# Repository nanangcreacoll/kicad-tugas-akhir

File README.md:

# Desain Skematik dan PCB IoT Liquid Dispensing Kapsul Radiofarmaka I-131

**Skematik**

**PCB**

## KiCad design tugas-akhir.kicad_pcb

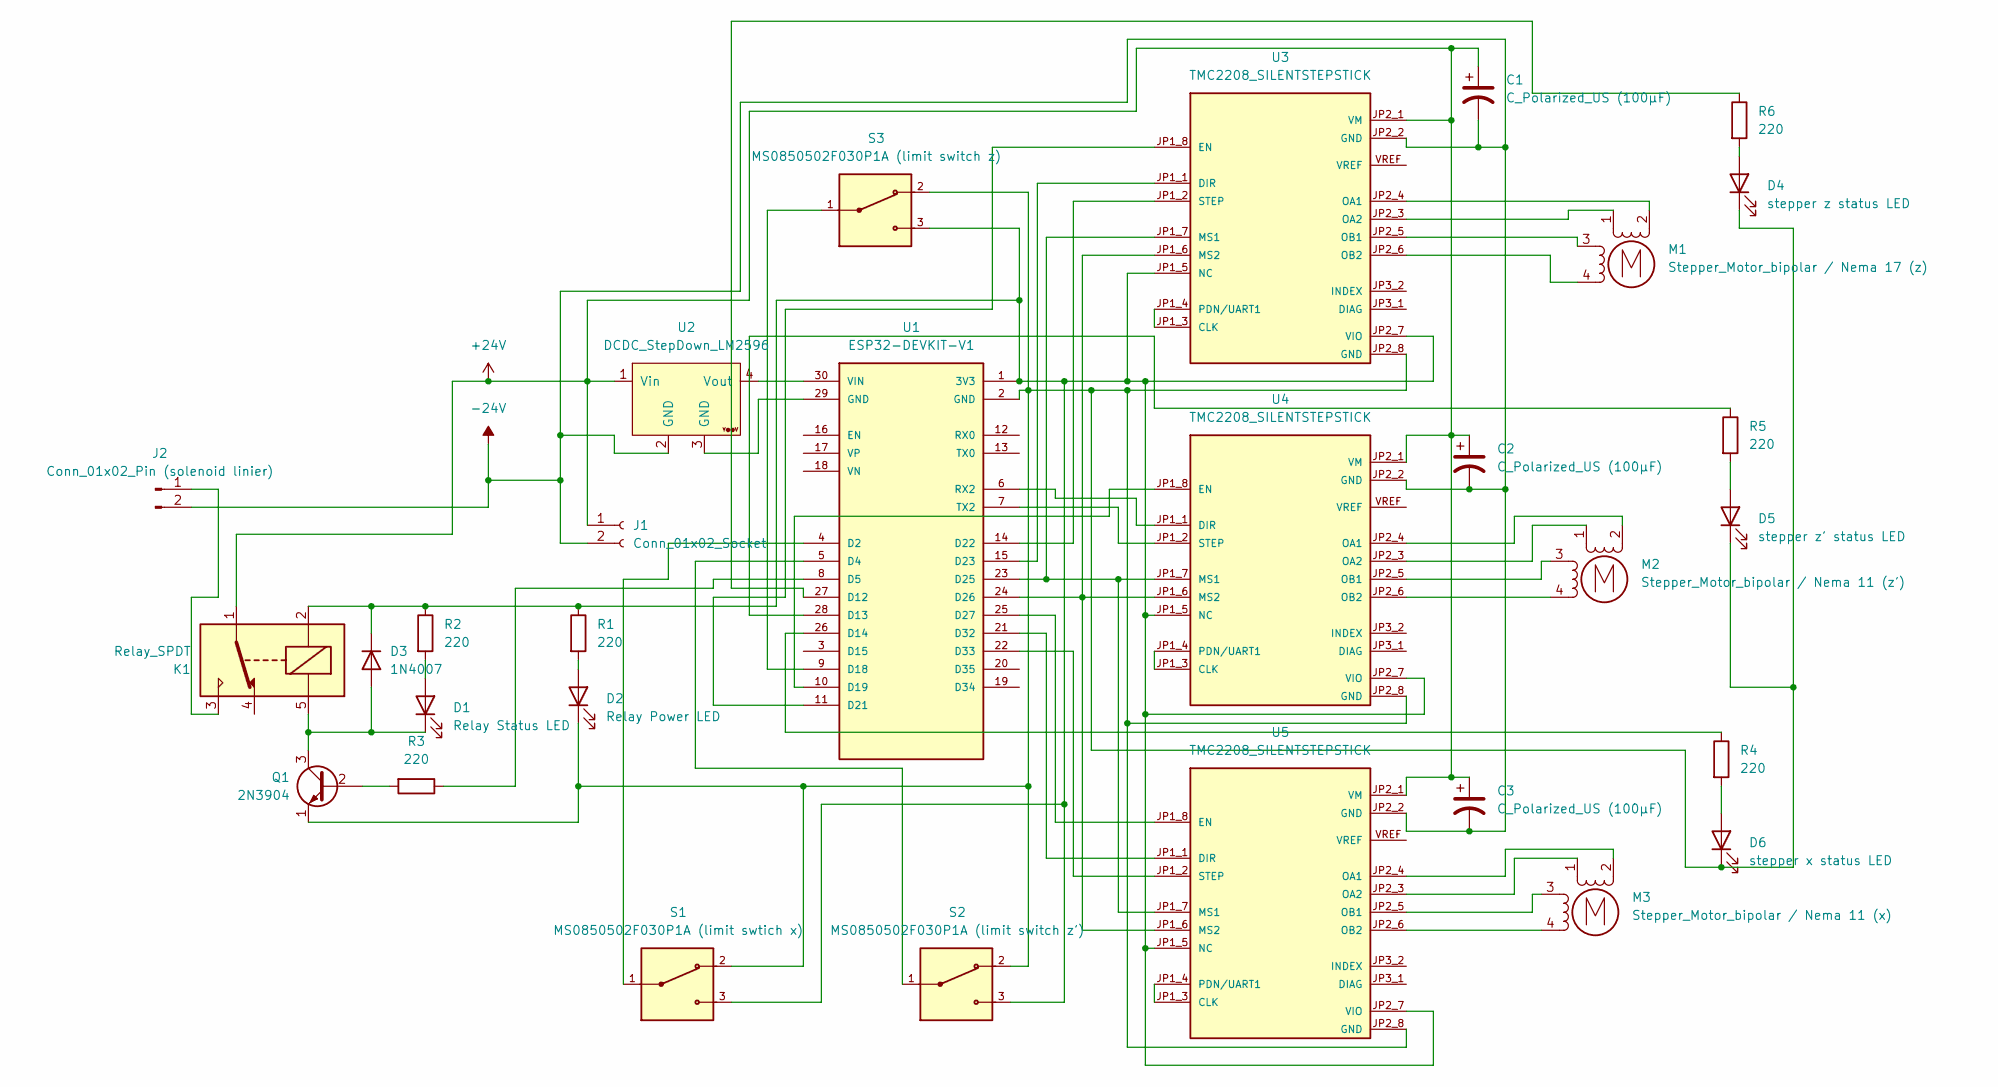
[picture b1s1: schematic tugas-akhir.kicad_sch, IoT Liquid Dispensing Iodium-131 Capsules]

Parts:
C1, C2, C3: C_Polarized_US (100μF); CP_Radial_D8.0mm_P3.50mm
D1: Relay Status LED; LED_D3.0mm
D2: Relay Power LED; LED_D3.0mm
D3: 1N4007; D_DO-41_SOD81_P7.62mm_Horizontal
D4: stepper z status LED; LED_D3.0mm
D5: stepper z' status LED; LED_D3.0mm
D6: stepper x status LED; LED_D3.0mm
J1: Conn_01x02_Socket; TerminalBlock_Phoenix_PT-1,5-2-3.5-H_1x02_P3.50mm_Horizontal
J2: Conn_01x02_Pin (solenoid linier); PinHeader_1x02_P2.54mm_Vertical
K1: Relay_SPDT; Relay_SPDT_SANYOU_SRD_Series_Form_C
M1: Stepper_Motor_bipolar / Nema 17 (z); PinHeader_1x04_P2.54mm_Vertical
M2: Stepper_Motor_bipolar / Nema 11 (z'); PinHeader_1x04_P2.54mm_Vertical
M3: Stepper_Motor_bipolar / Nema 11 (x); PinHeader_1x04_P2.54mm_Vertical
Q1: 2N3904; TO-92_Inline_Wide
R1, R2, R3, R4, R5, R6: 220; R_Axial_DIN0204_L3.6mm_D1.6mm_P7.62mm_Horizontal
S1: MS0850502F030P1A (limit swtich x); PinHeader_1x03_P2.54mm_Vertical
S2: MS0850502F030P1A (limit switch z'); PinHeader_1x03_P2.54mm_Vertical
S3: MS0850502F030P1A (limit switch z); PinHeader_1x03_P2.54mm_Vertical
U1: ESP32-DEVKIT-V1; MODULE_ESP32_DEVKIT_V1; PARTREV N/A
U2: DCDC_StepDown_LM2596
U3, U4, U5: TMC2208_SILENTSTEPSTICK; MODULE_TMC2208_SILENTSTEPSTICK

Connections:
3V3: D3.1 (K), K1.2, R1.1, R2.1, S1.3, S2.3, S3.3, U1.1 (3V3), U3.JP1_5 (NC), U3.JP2_7 (VIO), U4.JP1_5 (NC), U4.JP2_7 (VIO), U5.JP1_5 (NC), U5.JP2_7 (VIO)
GND: D2.1 (K), D4.1 (K), D5.1 (K), D6.1 (K), Q1.1 (E), S1.2, S2.2, S3.2, U1.2 (GND), U3.JP2_8 (GND), U4.JP2_8 (GND), U5.JP2_8 (GND); also elsewhere on the board
MS1: U1.23 (D25), U3.JP1_7 (MS1), U4.JP1_7 (MS1), U5.JP1_7 (MS1)
MS2: U1.24 (D26), U3.JP1_6 (MS2), U4.JP1_6 (MS2), U5.JP1_6 (MS2)
unnamed: D1.2 (A), R2.2
unnamed: D1.1 (K), D3.2 (A), K1.5, Q1.3 (C)
unnamed: D2.2 (A), R1.2
unnamed: D4.2 (A), R6.2
unnamed: D5.2 (A), R5.2
unnamed: D6.2 (A), R4.2
unnamed: J2.1, K1.3
unnamed: M1.2 (-), U3.JP2_4 (OA1)
unnamed: M2.2 (-), U4.JP2_4 (OA1)
unnamed: M3.2 (-), U5.JP2_4 (OA1)
unnamed: Q1.2 (B), R3.2
unnamed 15: U1.16 (EN); also elsewhere on the board
unnamed: U1.29 (GND), U2.3 (GND)
unnamed: U1.30 (VIN), U2.4 (Vout)
unnamed: U3.JP1_3 (CLK), U3.JP1_4 (PDN/UART1)
unnamed: M1.1, U3.JP2_3 (OA2)
unnamed: M1.3, U3.JP2_5 (OB1)
unnamed: M1.4, U3.JP2_6 (OB2)
unnamed: U4.JP1_3 (CLK), U4.JP1_4 (PDN/UART1)
unnamed: M2.1, U4.JP2_3 (OA2)
unnamed: M2.3, U4.JP2_5 (OB1)
unnamed: M2.4, U4.JP2_6 (OB2)
unnamed: U5.JP1_3 (CLK), U5.JP1_4 (PDN/UART1)
unnamed: M3.1, U5.JP2_3 (OA2)
unnamed: M3.3, U5.JP2_5 (OB1)
unnamed: M3.4, U5.JP2_6 (OB2)
RELAY: R3.1, U1.8 (D5)
V+: C1.1, C2.1, C3.1, J1.1, K1.1, U2.1 (Vin), U3.JP2_1 (VM), U4.JP2_1 (VM), U5.JP2_1 (VM)
V-: C1.2, C2.2, C3.2, J1.2, J2.2, U2.2 (GND), U3.JP2_2 (GND), U4.JP2_2 (GND), U5.JP2_2 (GND)
X_DIR: U1.21 (D32), U5.JP1_1 (DIR)
X_EN: U1.25 (D27), U5.JP1_8 (EN)
X_LED: R4.1, U1.26 (D14)
X_STEP: U1.22 (D33), U5.JP1_2 (STEP)
X_SW: S1.1, U1.4 (D2)
ZP_DIR: U1.6 (RX2), U4.JP1_1 (DIR)
ZP_EN: U1.10 (D19), U4.JP1_8 (EN)
ZP_LED: R5.1, U1.28 (D13)
ZP_STEP: U1.7 (TX2), U4.JP1_2 (STEP)
ZP_SW: S2.1, U1.5 (D4)
Z_DIR: U1.15 (D23), U3.JP1_1 (DIR)
Z_EN: U1.11 (D21), U3.JP1_8 (EN)
Z_LED: R6.1, U1.27 (D12)
Z_STEP: U1.14 (D22), U3.JP1_2 (STEP)
Z_SW: S3.1, U1.9 (D18)

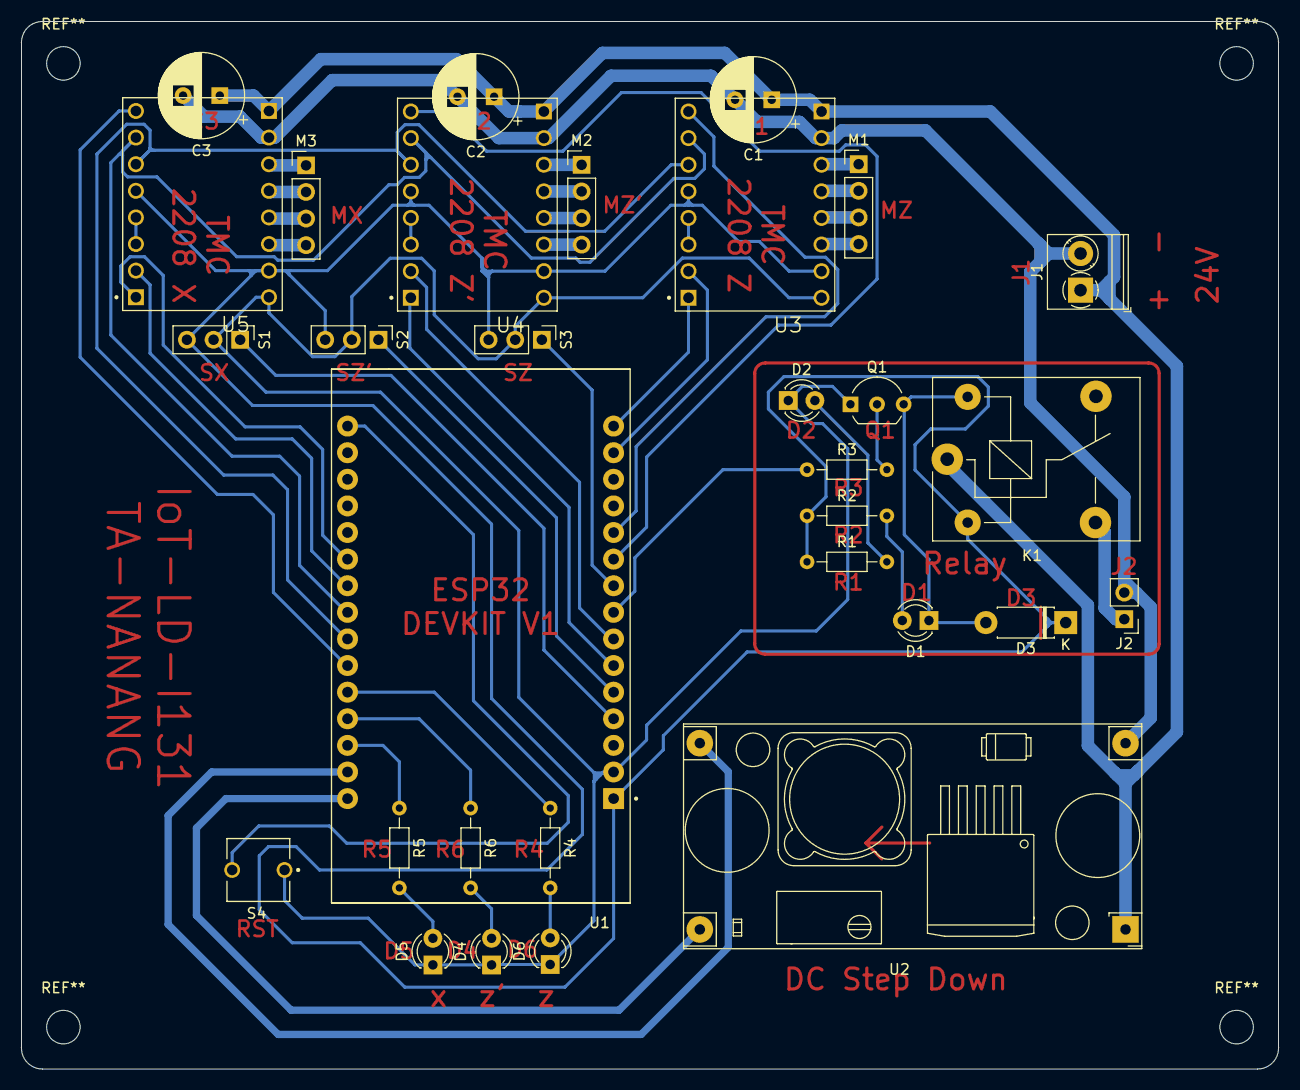
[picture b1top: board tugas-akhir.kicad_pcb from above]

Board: 2 copper layers, 120.0 x 100.0 mm, 31 parts (0 on the bottom side), 48 nets.

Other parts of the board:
S4: RESET BUTTON; SW_BUTT-2

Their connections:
GND: S4.1; also elsewhere on the board
unnamed 15: S4.2; also elsewhere on the board

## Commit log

2024-04-19 route relay module
2024-04-22 update route
2024-04-22 route stepper driver
2024-04-25 feat: new route
2024-04-25 finish pcb route
2024-04-26 add fabrication outputs
2024-04-30 nothing
2024-04-30 new pcb route
2024-05-16 change size of resistor and terminal block
2024-05-19 minor revision
2024-05-19 add readme
2024-05-20 update driver routes
2024-05-22 add reset button and refactor schematic
2024-05-23 minor changes
2024-05-27 change drill to single file
